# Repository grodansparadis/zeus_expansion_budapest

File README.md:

<h1>Zeus Expansion Budapest</h1>

Olimex UEXT add on card with Zeus expansion connector. Fits the 
<a href="http://www.grodansparadis.com/odessa/odessa.html">Odessa</a> module
among other modules.

<hr>

This project is part of the <a href="http://www.vscp.org">VSCP (Very Simple Control Protocol) project</a>. 

<hr>

This project is licensed under the 
<a href="http://creativecommons.org/licenses/by-nc-sa/3.0/">Creative Commons open source license Attribution-NonCommercial-ShareAlike 3.0 Unported</a>. 
Other license options are available by conacting <a href="malto:info@grodansparadis.com">Paradis of the Frog AB</a>

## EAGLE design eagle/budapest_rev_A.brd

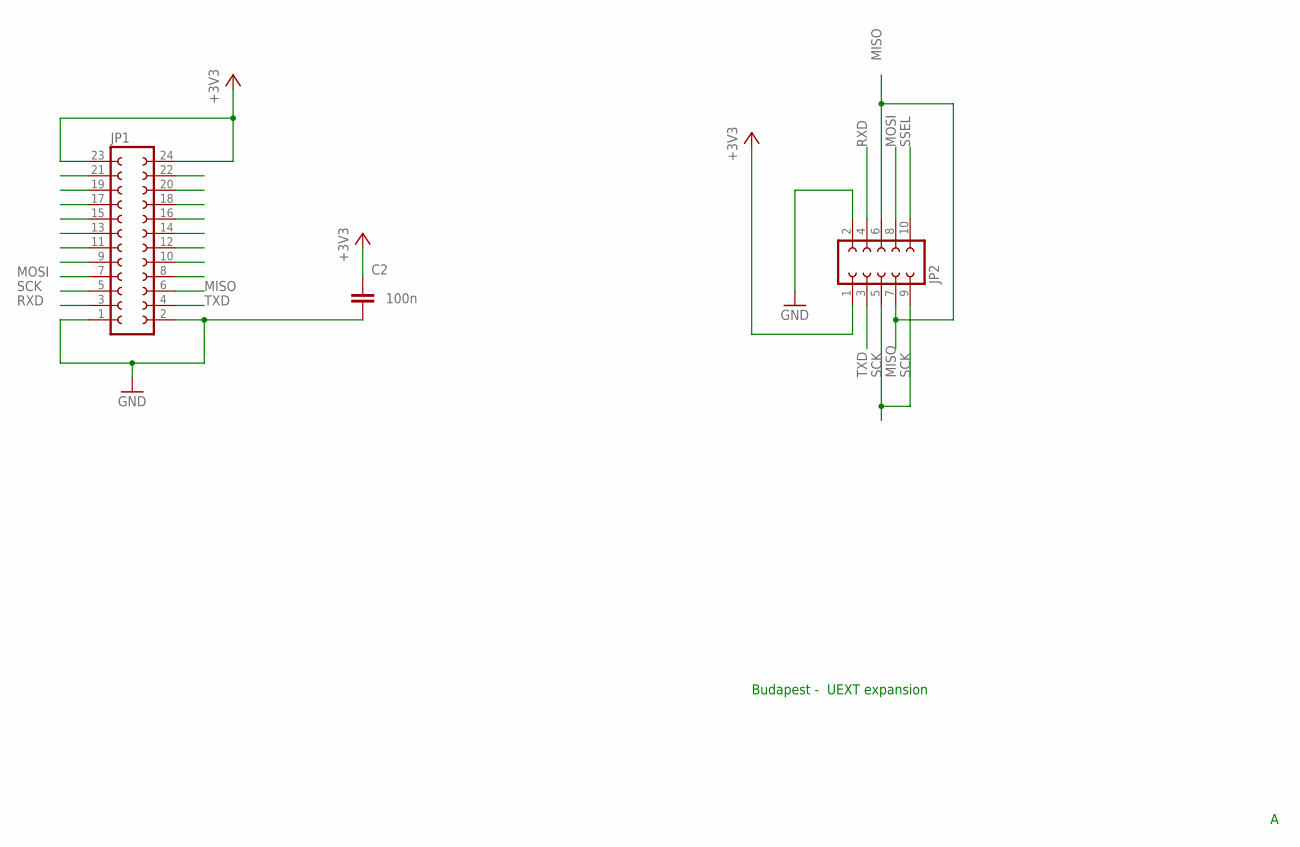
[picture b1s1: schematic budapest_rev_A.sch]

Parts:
C2: 100n; C0805
JP1: FE12-2
JP2: FE05-2

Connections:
+3V3: C2.1, JP1.23, JP1.24, JP2.1
GND: C2.2, JP1.1, JP1.2, JP2.2
MISO: JP1.6, JP2.6, JP2.7
MOSI: JP1.7, JP2.8
RXD: JP1.3, JP2.4
SCK: JP1.5, JP2.5, JP2.9
SSEL: JP2.10
TXD: JP1.4, JP2.3

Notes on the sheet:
Budapest - UEXT expansion

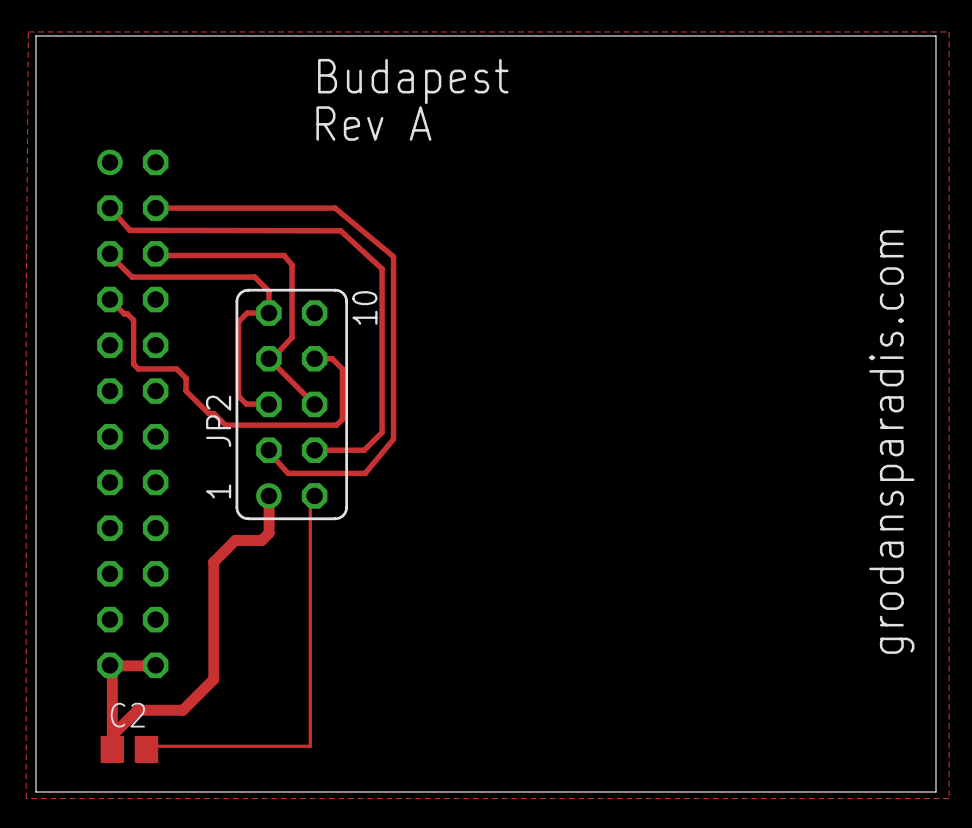
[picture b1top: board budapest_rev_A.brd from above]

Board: 2 copper layers, 50.0 x 42.0 mm, 3 parts (1 on the bottom side), 7 nets.

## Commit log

2015-11-03 Making design open
2015-12-17 Updated license and readme
